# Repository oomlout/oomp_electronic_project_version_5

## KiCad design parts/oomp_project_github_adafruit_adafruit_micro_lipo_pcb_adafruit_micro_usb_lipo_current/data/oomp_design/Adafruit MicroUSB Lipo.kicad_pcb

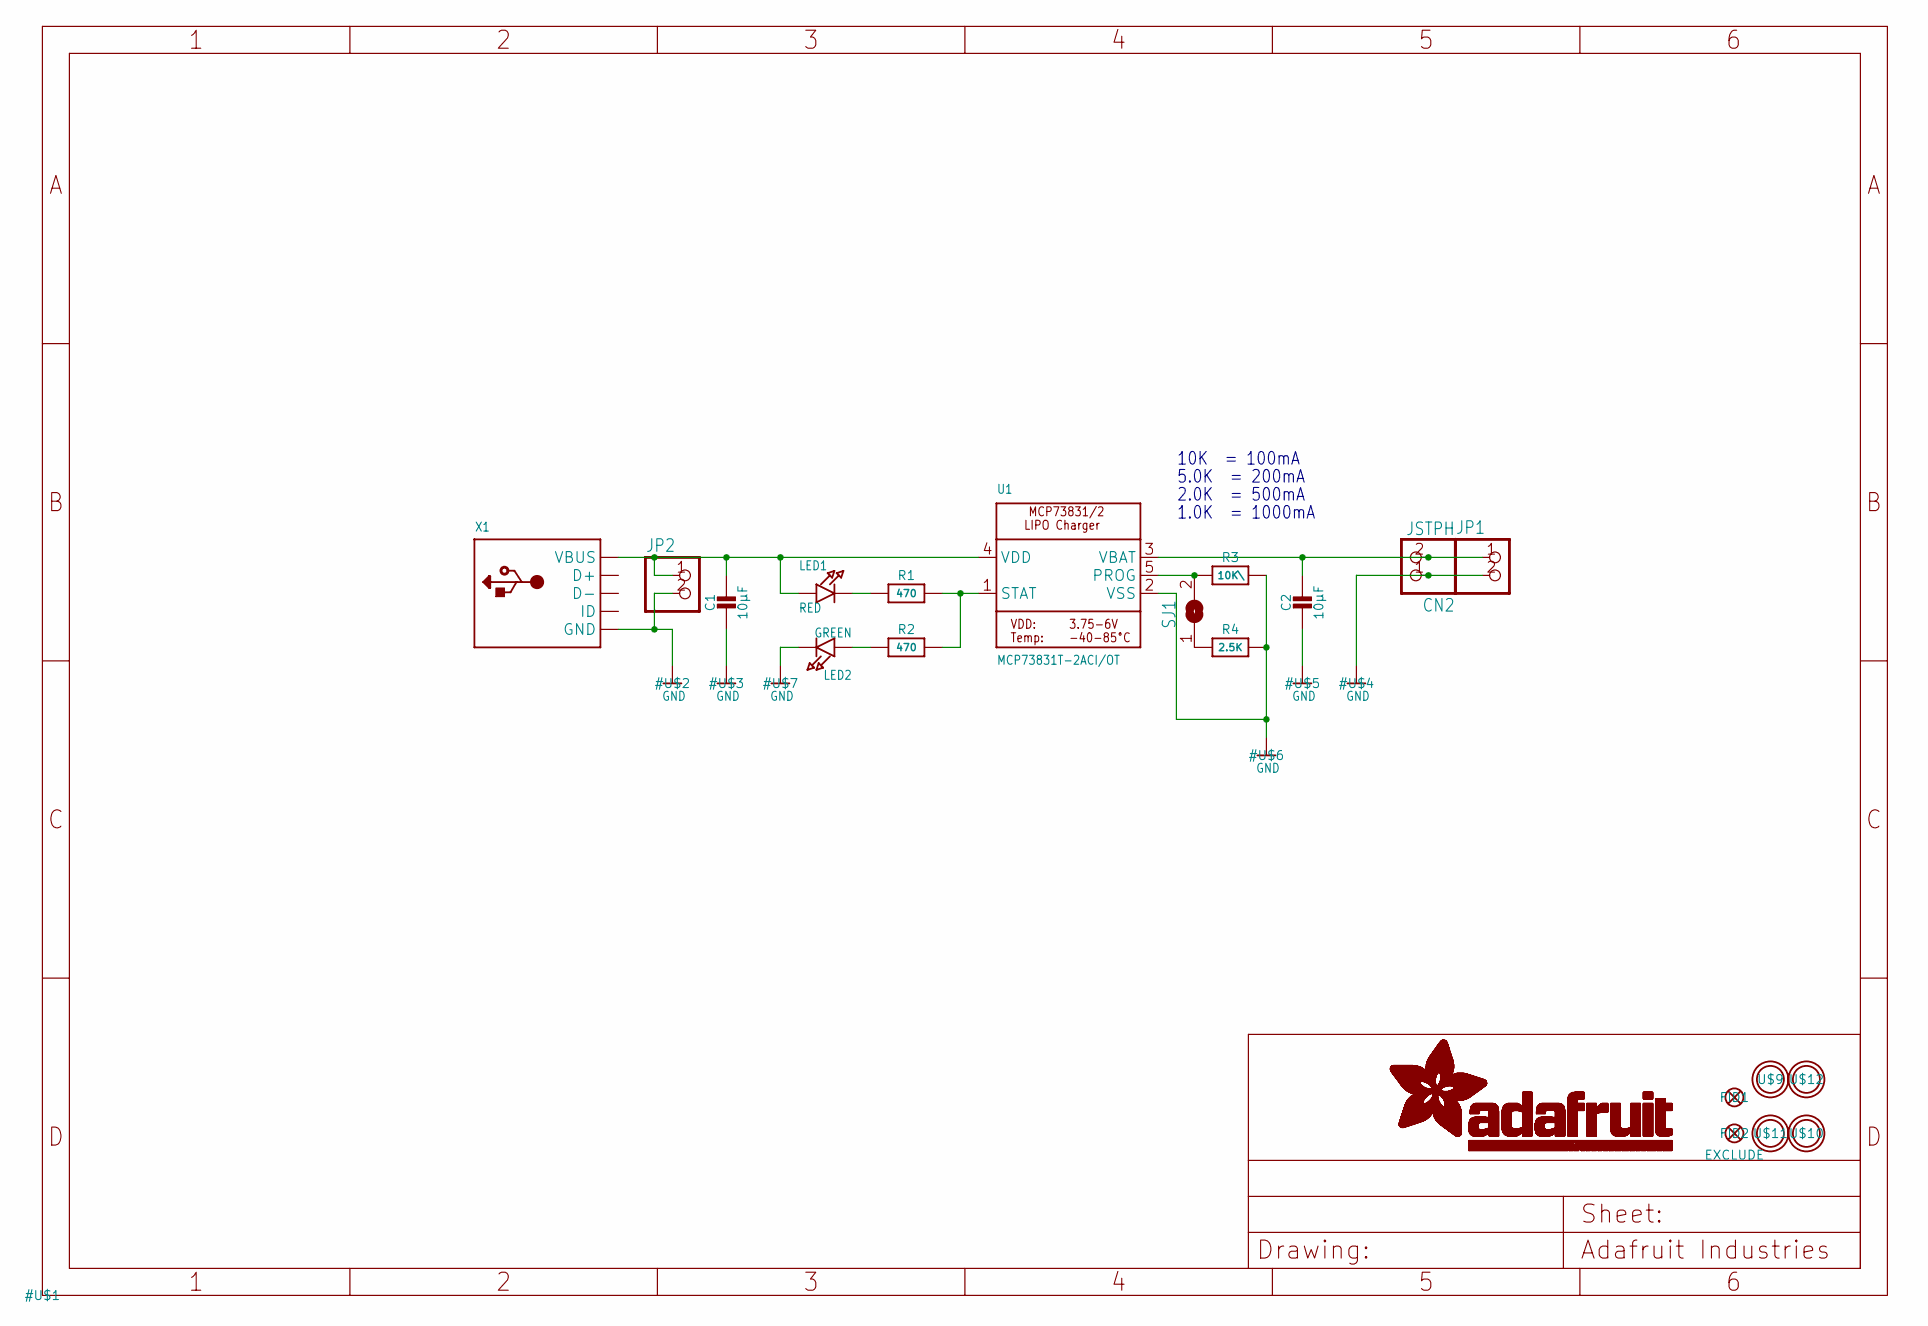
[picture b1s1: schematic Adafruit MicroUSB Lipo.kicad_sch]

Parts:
C1, C2: 10µF; 0805-NO
CN2: JSTPH; JSTPH2
FID1, FID2: FIDUCIAL""; FIDUCIAL_1MM
JP1, JP2: HEADER-1X2ROUND; 1X02_ROUND
LED1: RED; CHIPLED_0805_NOOUTLINE
LED2: GREEN; CHIPLED_0805_NOOUTLINE
R1, R2: 470; 0805-NO
R3: 10K\; 0805-NO
R4: 2.5K; 0805-NO
SJ1: SOLDERJUMPER; SOLDERJUMPER_ARROW_NOPASTE
U1: MCP73831T-2ACI/OT; SOT23-5
U$9, U$10, U$11, U$12: MOUNTINGHOLE2.5; MOUNTINGHOLE_2.5_PLATED
X1: USBMICRO_20329; 4UCONN_20329

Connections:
GND: C1.2, C2.2, CN2.1, JP1.2, JP2.2, LED2.C, R3.2, R4.2, U1.2 (VSS), X1.BASE@1 (GND), X1.BASE@2 (GND), X1.GND, X1.SPRT@1 (GND), X1.SPRT@2 (GND), X1.SPRT@3 (GND), X1.SPRT@4 (GND)
unnamed: LED1.C, R1.1
unnamed: R1.2, R2.2, U1.1 (STAT)
unnamed: R4.1, SJ1.1
unnamed: R3.1, SJ1.2, U1.5 (PROG)
unnamed: LED2.A, R2.1
VBAT: C2.1, CN2.2, JP1.1, U1.3 (VBAT)
VDD: C1.1, JP2.1, LED1.A, U1.4 (VDD), X1.VBUS

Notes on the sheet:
2.0K = 500mA
1.0K = 1000mA
5.0K = 200mA
10K = 100mA

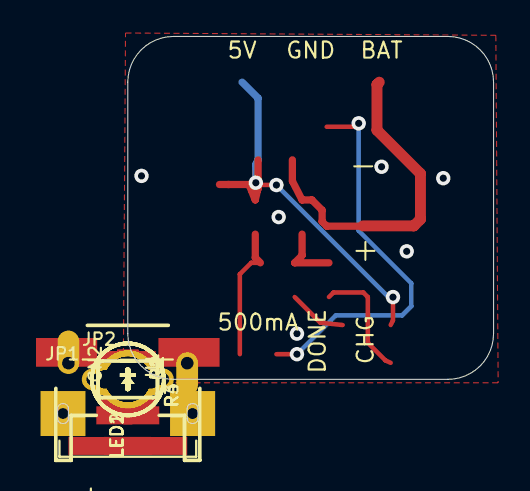
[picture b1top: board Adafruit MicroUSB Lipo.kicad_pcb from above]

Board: 2 copper layers, 20.3 x 19.1 mm, 21 parts (1 on the bottom side), 8 nets.

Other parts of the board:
U$13: ADAFRUIT_5MM

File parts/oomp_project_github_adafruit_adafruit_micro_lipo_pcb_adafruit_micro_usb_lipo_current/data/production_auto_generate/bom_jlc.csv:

Comment,Designator,Footprint,LCSC Part #
,"JP1,JP2",Adafruit MicroUSB Lipo-import-fps:1X02_ROUND,C492401
,X1,Adafruit MicroUSB Lipo-import-fps:4UCONN_20329,
,U$13,Adafruit MicroUSB Lipo-import-fps:ADAFRUIT_5MM,
10K\,R3,Adafruit MicroUSB Lipo-import-fps:0805-NO,C17414
10µF,"C1,C2",Adafruit MicroUSB Lipo-import-fps:0805-NO,
2.5K,R4,Adafruit MicroUSB Lipo-import-fps:0805-NO,
470,"R1,R2",Adafruit MicroUSB Lipo-import-fps:0805-NO,C17710
GREEN,LED2,Adafruit MicroUSB Lipo-import-fps:CHIPLED_0805_NOOUTLINE,
JSTPH,CN2,Adafruit MicroUSB Lipo-import-fps:JSTPH2,
MCP73831T-2ACI/OT,U1,Adafruit MicroUSB Lipo-import-fps:SOT23-5,
RED,LED1,Adafruit MicroUSB Lipo-import-fps:CHIPLED_0805_NOOUTLINE,

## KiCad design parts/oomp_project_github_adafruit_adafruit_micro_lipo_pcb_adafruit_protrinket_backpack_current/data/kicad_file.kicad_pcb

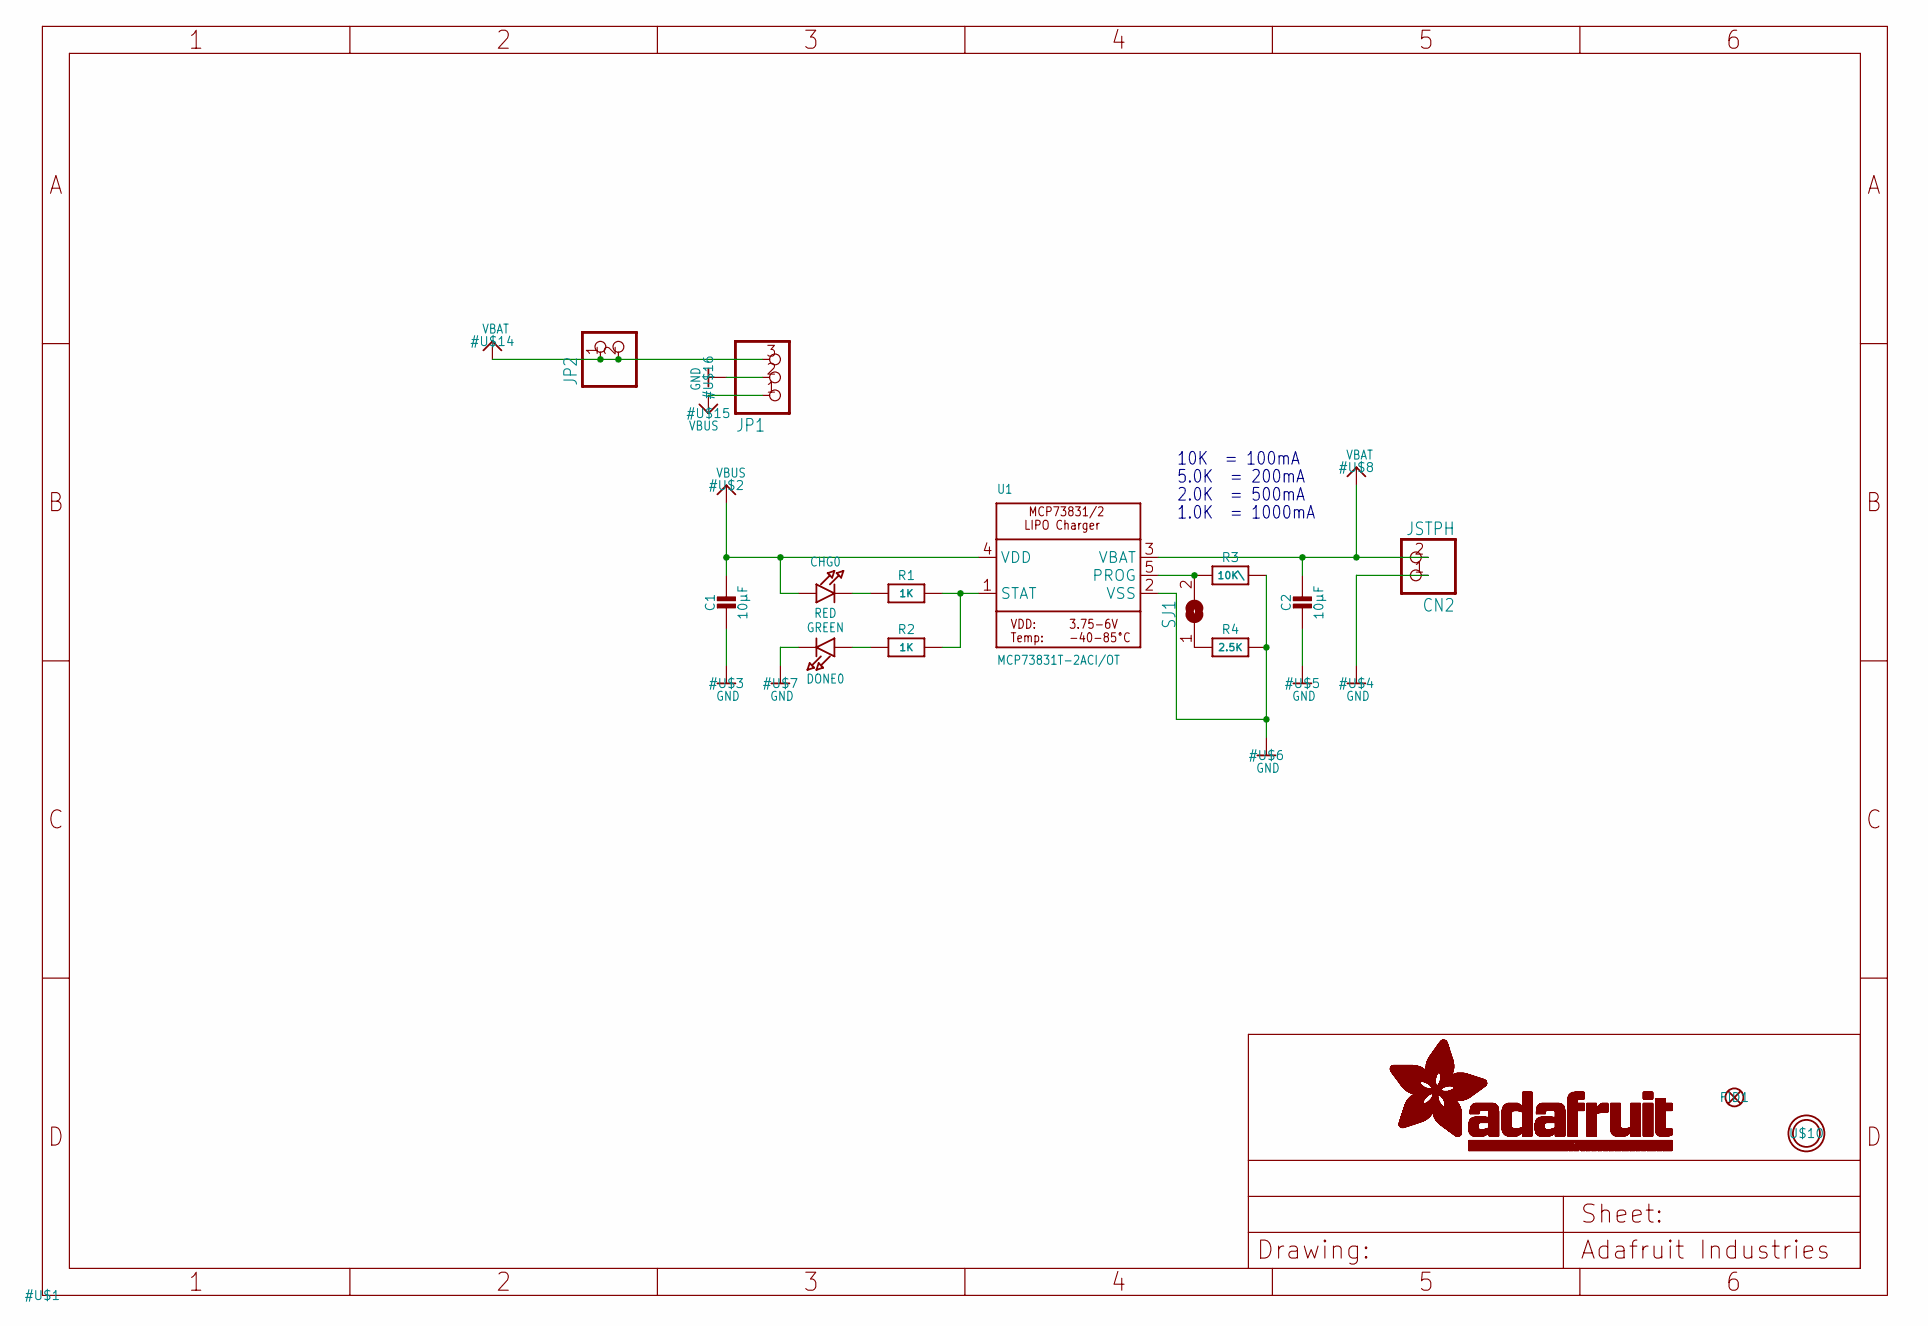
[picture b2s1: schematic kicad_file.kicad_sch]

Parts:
C1, C2: 10µF; 0805-NO
CHG0: RED; CHIPLED_0805_NOOUTLINE
CN2: JSTPH; JSTPH2
DONE0: GREEN; CHIPLED_0805_NOOUTLINE
FID1: FIDUCIAL""; FIDUCIAL_1MM
JP1: HEADER-1X376MIL; 1X03_ROUND_76
JP2: HEADER-1X2ROUND; 1X02_ROUND
R1, R2: 1K; 0805-NO
R3: 10K\; _0805MP
R4: 2.5K; 0805-NO
SJ1: SOLDERJUMPER; SOLDERJUMPER_ARROW_NOPASTE
U1: MCP73831T-2ACI/OT; SOT23-5
U$10: MOUNTINGHOLE2.5; MOUNTINGHOLE_2.5_PLATED

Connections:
GND: C1.2, C2.2, CN2.1, DONE0.C, JP1.2, R3.2, R4.2, U1.2 (VSS)
unnamed: CHG0.C, R1.1
unnamed: R1.2, R2.2, U1.1 (STAT)
unnamed: R4.1, SJ1.1
unnamed: R3.1, SJ1.2, U1.5 (PROG)
unnamed: DONE0.A, R2.1
VBAT: C2.1, CN2.2, JP1.3, JP2.1, JP2.2, U1.3 (VBAT)
VBUS: C1.1, CHG0.A, JP1.1, U1.4 (VDD)

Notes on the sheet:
2.0K = 500mA
1.0K = 1000mA
5.0K = 200mA
10K = 100mA

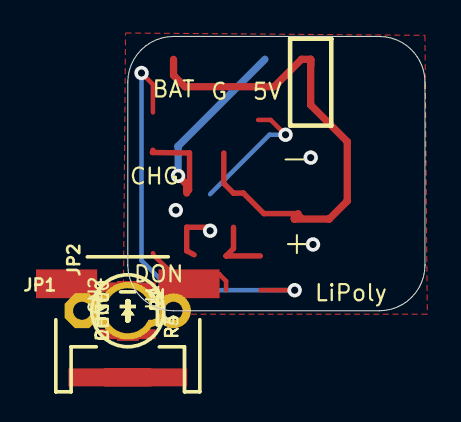
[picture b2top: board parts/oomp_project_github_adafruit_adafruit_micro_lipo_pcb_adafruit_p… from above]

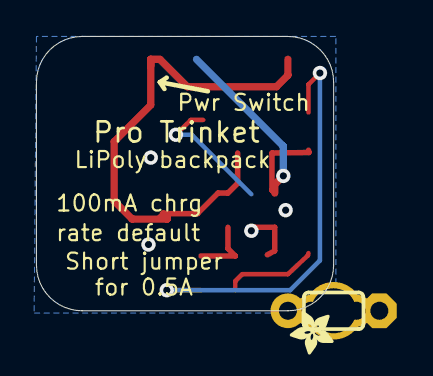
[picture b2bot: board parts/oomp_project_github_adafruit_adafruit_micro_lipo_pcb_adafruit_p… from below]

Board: 2 copper layers, 16.5 x 15.2 mm, 16 parts (2 on the bottom side), 8 nets.

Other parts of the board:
U$9: ADAFRUIT_2.5MM

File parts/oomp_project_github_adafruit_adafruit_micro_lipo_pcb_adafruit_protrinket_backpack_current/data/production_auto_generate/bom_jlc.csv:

Comment,Designator,Footprint,LCSC Part #
,JP2,Adafruit protrinket backpack-import-fps:1X02_ROUND,C492401
,JP1,Adafruit protrinket backpack-import-fps:1X03_ROUND_76,C49257
,U$9,Adafruit protrinket backpack-import-fps:ADAFRUIT_2.5MM,
10K\,R3,Adafruit protrinket backpack-import-fps:_0805MP,C17414
10µF,"C1,C2",Adafruit protrinket backpack-import-fps:0805-NO,
1K,"R1,R2",Adafruit protrinket backpack-import-fps:0805-NO,C17513
2.5K,R4,Adafruit protrinket backpack-import-fps:0805-NO,
GREEN,DONE0,Adafruit protrinket backpack-import-fps:CHIPLED_0805_NOOUTLINE,
JSTPH,CN2,Adafruit protrinket backpack-import-fps:JSTPH2,
MCP73831T-2ACI/OT,U1,Adafruit protrinket backpack-import-fps:SOT23-5,
RED,CHG0,Adafruit protrinket backpack-import-fps:CHIPLED_0805_NOOUTLINE,

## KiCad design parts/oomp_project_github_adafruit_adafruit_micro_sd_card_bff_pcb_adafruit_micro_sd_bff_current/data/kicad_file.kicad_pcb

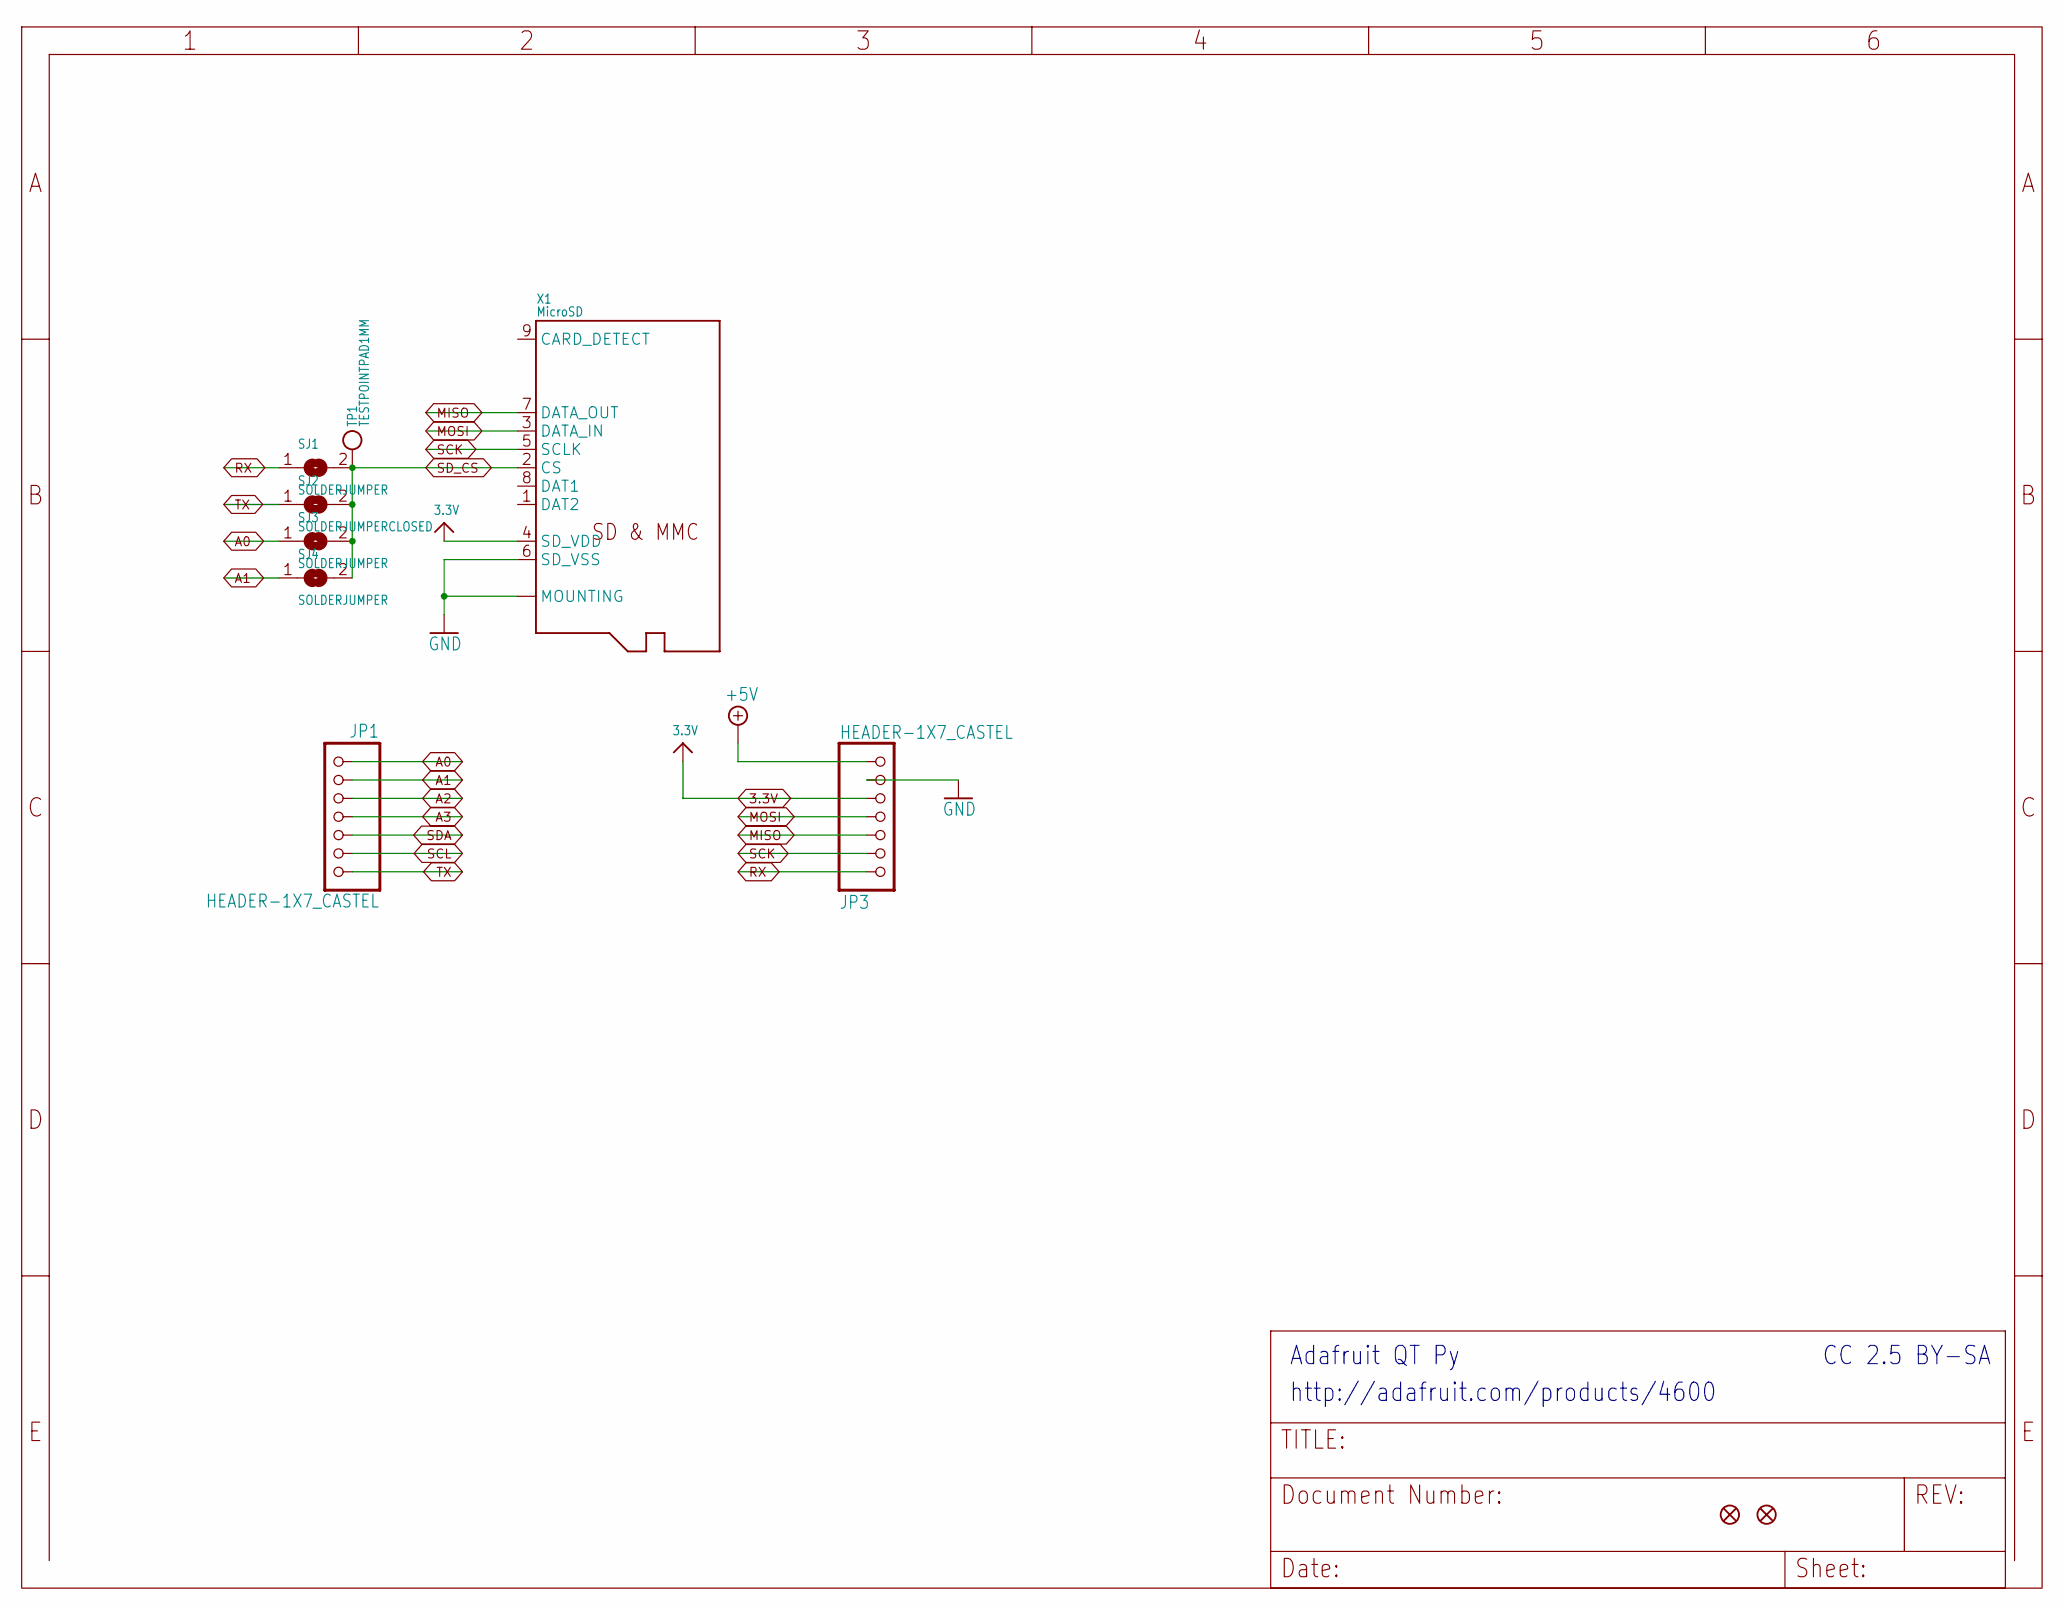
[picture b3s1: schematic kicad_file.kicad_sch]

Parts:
JP1, JP3: HEADER-1X7_CASTEL; 1X07_CASTEL
SJ1, SJ3, SJ4: SOLDERJUMPER; SOLDERJUMPER_ARROW_NOPASTE
SJ2: SOLDERJUMPERCLOSED; SOLDERJUMPER_CLOSEDWIRE
TP1: TESTPOINTPAD1MM; TESTPOINT_PAD_1MM
U$6, U$8: FIDUCIAL_1MM
X1: MicroSD; MOLEX_104031-0811

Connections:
3.3V: JP3.5, JP3.5C (5), X1.4 (SD_VDD)
+5V: JP3.7, JP3.7C (7)
A0: JP1.1, JP1.1C (1), SJ3.1
A1: JP1.2, JP1.2C (2), SJ4.1
A2: JP1.3, JP1.3C (3)
A3: JP1.4, JP1.4C (4)
GND: JP3.6, JP3.6C (6), X1.6 (SD_VSS), X1.10 (MOUNTING), X1.G1 (MOUNTING), X1.G2 (MOUNTING), X1.G3 (MOUNTING), X1.G4 (MOUNTING)
MISO: JP3.3, JP3.3C (3), X1.7 (DATA_OUT)
MOSI: JP3.4, JP3.4C (4), X1.3 (DATA_IN)
RX: JP3.1, JP3.1C (1), SJ1.1
SCK: JP3.2, JP3.2C (2), X1.5 (SCLK)
SCL: JP1.6, JP1.6C (6)
SDA: JP1.5, JP1.5C (5)
SD_CS: SJ1.2, SJ2.2, SJ3.2, SJ4.2, TP1.P$1, X1.2 (CS)
TX: JP1.7, JP1.7C (7), SJ2.1

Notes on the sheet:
CC 2.5 BY-SA
Adafruit QT Py
http://adafruit.com/products/4600

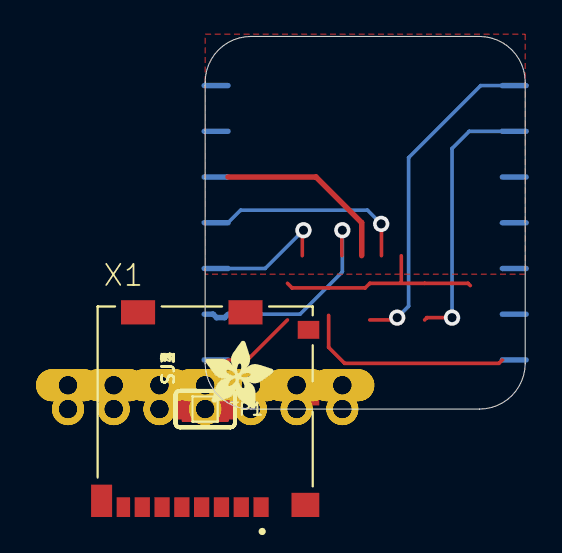
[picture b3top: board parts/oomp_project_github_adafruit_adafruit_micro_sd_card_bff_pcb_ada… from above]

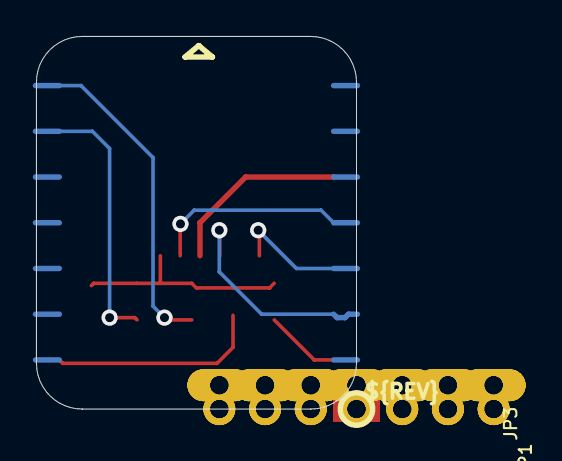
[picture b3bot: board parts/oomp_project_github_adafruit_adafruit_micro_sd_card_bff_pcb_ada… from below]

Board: 16 copper layers, 17.8 x 20.7 mm, 20 parts (5 on the bottom side), 15 nets.

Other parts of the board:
PLABEL0: PLABEL0
PLABEL1: PLABEL1
PLABEL2: PLABEL2
PLABEL3: PLABEL3
PLABEL4: PLABEL4
PLABEL5: PLABEL5
PLABEL6: PLABEL6
PLABEL7: PLABEL7
U$2: ADAFRUIT_3.5MM
U$3: PCBFEAT-REV-040

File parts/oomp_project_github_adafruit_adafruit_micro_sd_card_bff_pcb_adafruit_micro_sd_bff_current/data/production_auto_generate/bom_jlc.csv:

Comment,Designator,Footprint,LCSC Part #
,"JP1,JP3",Adafruit microSD BFF-import-fps:1X07_CASTEL,C7501585
,U$2,Adafruit microSD BFF-import-fps:ADAFRUIT_3.5MM,
,U$3,Adafruit microSD BFF-import-fps:PCBFEAT-REV-040,
,PLABEL0,Adafruit microSD BFF-import-fps:PLABEL0,
,PLABEL1,Adafruit microSD BFF-import-fps:PLABEL1,
,PLABEL2,Adafruit microSD BFF-import-fps:PLABEL2,
,PLABEL3,Adafruit microSD BFF-import-fps:PLABEL3,
,PLABEL4,Adafruit microSD BFF-import-fps:PLABEL4,
,PLABEL5,Adafruit microSD BFF-import-fps:PLABEL5,
,PLABEL6,Adafruit microSD BFF-import-fps:PLABEL6,
,PLABEL7,Adafruit microSD BFF-import-fps:PLABEL7,
,TP1,Adafruit microSD BFF-import-fps:TESTPOINT_PAD_1MM,
FIDUCIAL_1MM,"U$6,U$8",Adafruit microSD BFF-import-fps:FIDUCIAL_1MM,
MicroSD,X1,Adafruit microSD BFF-import-fps:MOLEX_104031-0811,
